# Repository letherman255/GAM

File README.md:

GAM
===

Projet terminale sti2d

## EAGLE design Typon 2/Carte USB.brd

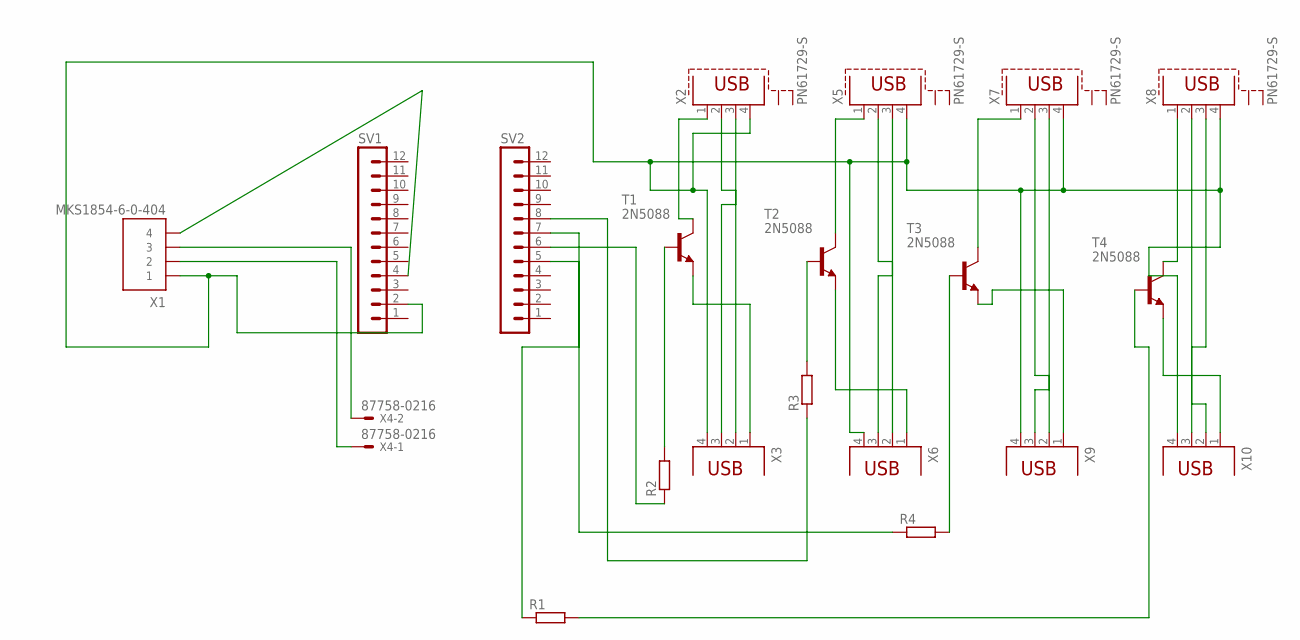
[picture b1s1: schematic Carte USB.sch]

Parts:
R1, R2, R3, R4: R-EU_0207/10; 0207/10
SV1, SV2: MA12-1
T1, T2, T3, T4: 2N5088; TO92
X1: MKS1854-6-0-404
X2, X5, X7, X8: PN61729-S
X3, X6, X9, X10: PN87520
X4: 87758-0216

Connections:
unnamed: X1.3, X4.2
unnamed: X1.2, X4.1
unnamed: T1.1 (C), X2.1
unnamed: X2.2, X3.2
unnamed: SV1.4, X1.4
unnamed: T2.1 (C), X5.1
unnamed: X2.3, X3.3
unnamed: X5.3, X6.3
unnamed: T2.3 (E), X6.1
unnamed: X5.2, X6.2
unnamed: T3.1 (C), X7.1
unnamed: X7.2, X9.2
unnamed: X7.3, X9.3
unnamed: T4.1 (C), X8.1
unnamed: X8.2, X10.2
unnamed: X8.3, X10.3
unnamed: SV1.2, X1.1, X2.4, X3.4, X5.4, X6.4, X7.4, X8.4, X9.4, X10.4
unnamed: T3.3 (E), X9.1
unnamed: T4.3 (E), X10.1
unnamed: T1.3 (E), X3.1
unnamed: R3.2, T2.2 (B)
unnamed: R4.2, T3.2 (B)
unnamed: R2.2, T1.2 (B)
unnamed: R1.2, T4.2 (B)
unnamed: R1.1, SV2.5
unnamed: R2.1, SV2.6
unnamed: R4.1, SV2.7
unnamed: R3.1, SV2.8

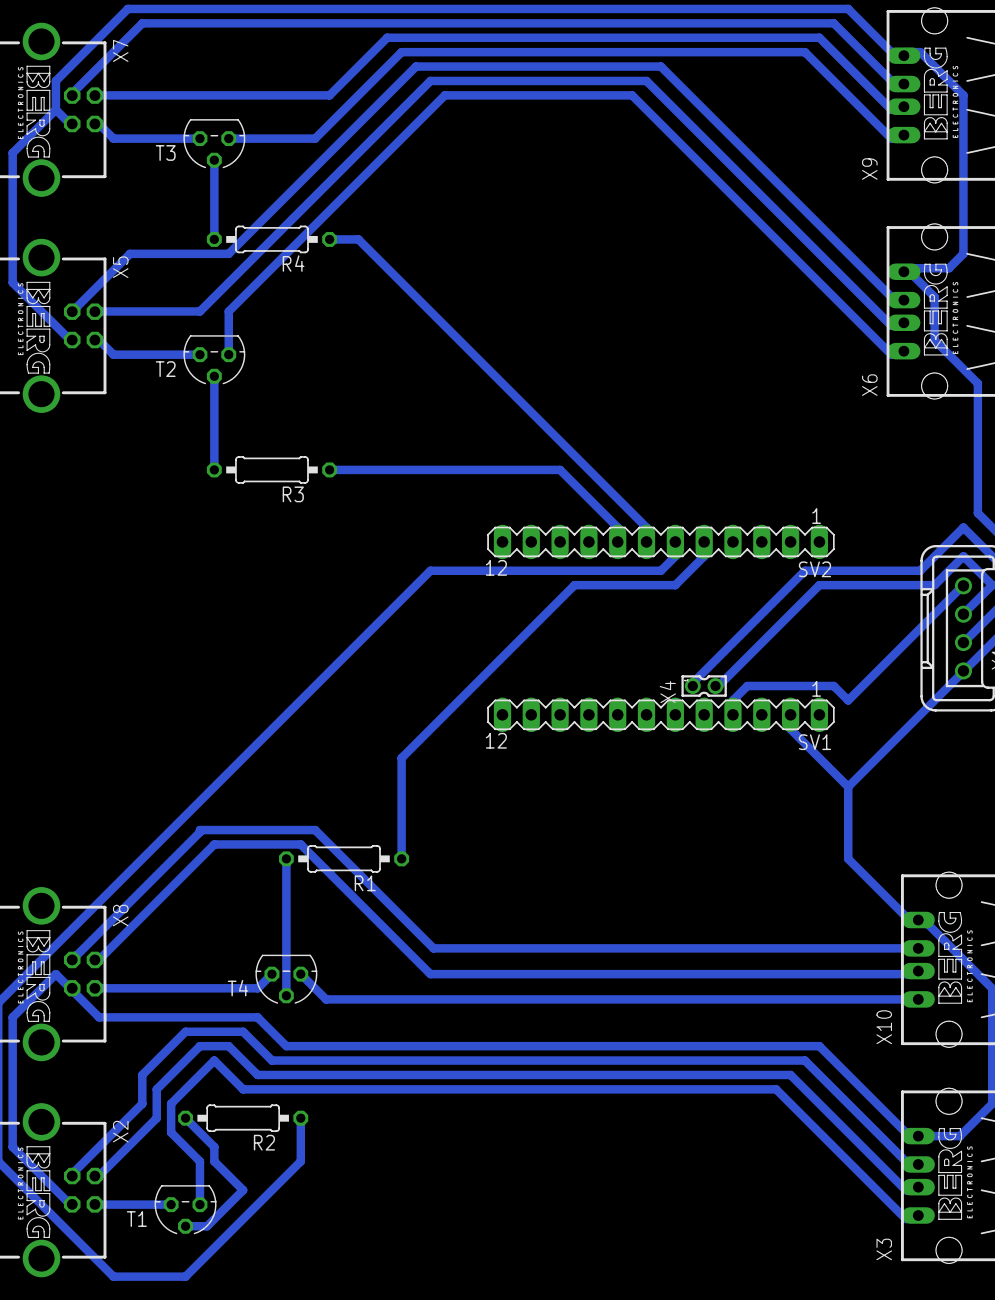
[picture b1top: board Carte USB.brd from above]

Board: 2 copper layers, 20 parts (0 on the bottom side), 28 nets.

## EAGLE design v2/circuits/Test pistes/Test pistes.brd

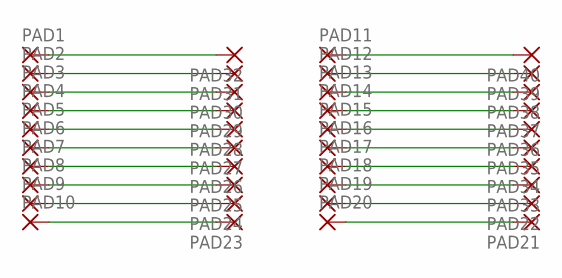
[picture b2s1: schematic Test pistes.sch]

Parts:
PAD1, PAD2, PAD3, PAD4, PAD5, PAD6, PAD7, PAD8, PAD9, PAD10, PAD11, PAD12, PAD13, PAD14, PAD15, PAD16, PAD17, PAD18, PAD19, PAD20, PAD21, PAD22, PAD23, PAD24, PAD25, PAD26, PAD27, PAD28, PAD29, PAD30, PAD31, PAD32, PAD33, PAD34, PAD35, PAD36, PAD37, PAD38, PAD39, PAD40: 2,54/1,1

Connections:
unnamed: PAD1.1, PAD32.1
unnamed: PAD2.1, PAD31.1
unnamed: PAD3.1, PAD30.1
unnamed: PAD4.1, PAD29.1
unnamed: PAD5.1, PAD28.1
unnamed: PAD6.1, PAD27.1
unnamed: PAD7.1, PAD26.1
unnamed: PAD8.1, PAD25.1
unnamed: PAD9.1, PAD24.1
unnamed: PAD10.1, PAD23.1
unnamed: PAD11.1, PAD40.1
unnamed: PAD12.1, PAD39.1
unnamed: PAD13.1, PAD38.1
unnamed: PAD14.1, PAD37.1
unnamed: PAD15.1, PAD36.1
unnamed: PAD16.1, PAD35.1
unnamed: PAD17.1, PAD34.1
unnamed: PAD18.1, PAD33.1
unnamed: PAD19.1, PAD22.1
unnamed: PAD20.1, PAD21.1

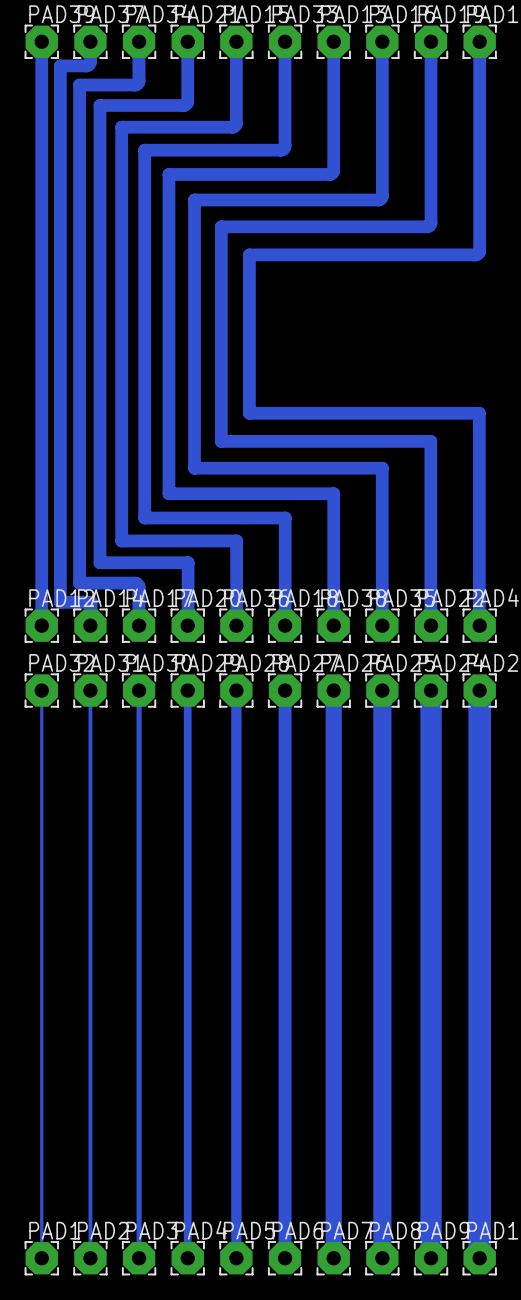
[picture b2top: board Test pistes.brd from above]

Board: 2 copper layers, 40 parts (0 on the bottom side), 20 nets.

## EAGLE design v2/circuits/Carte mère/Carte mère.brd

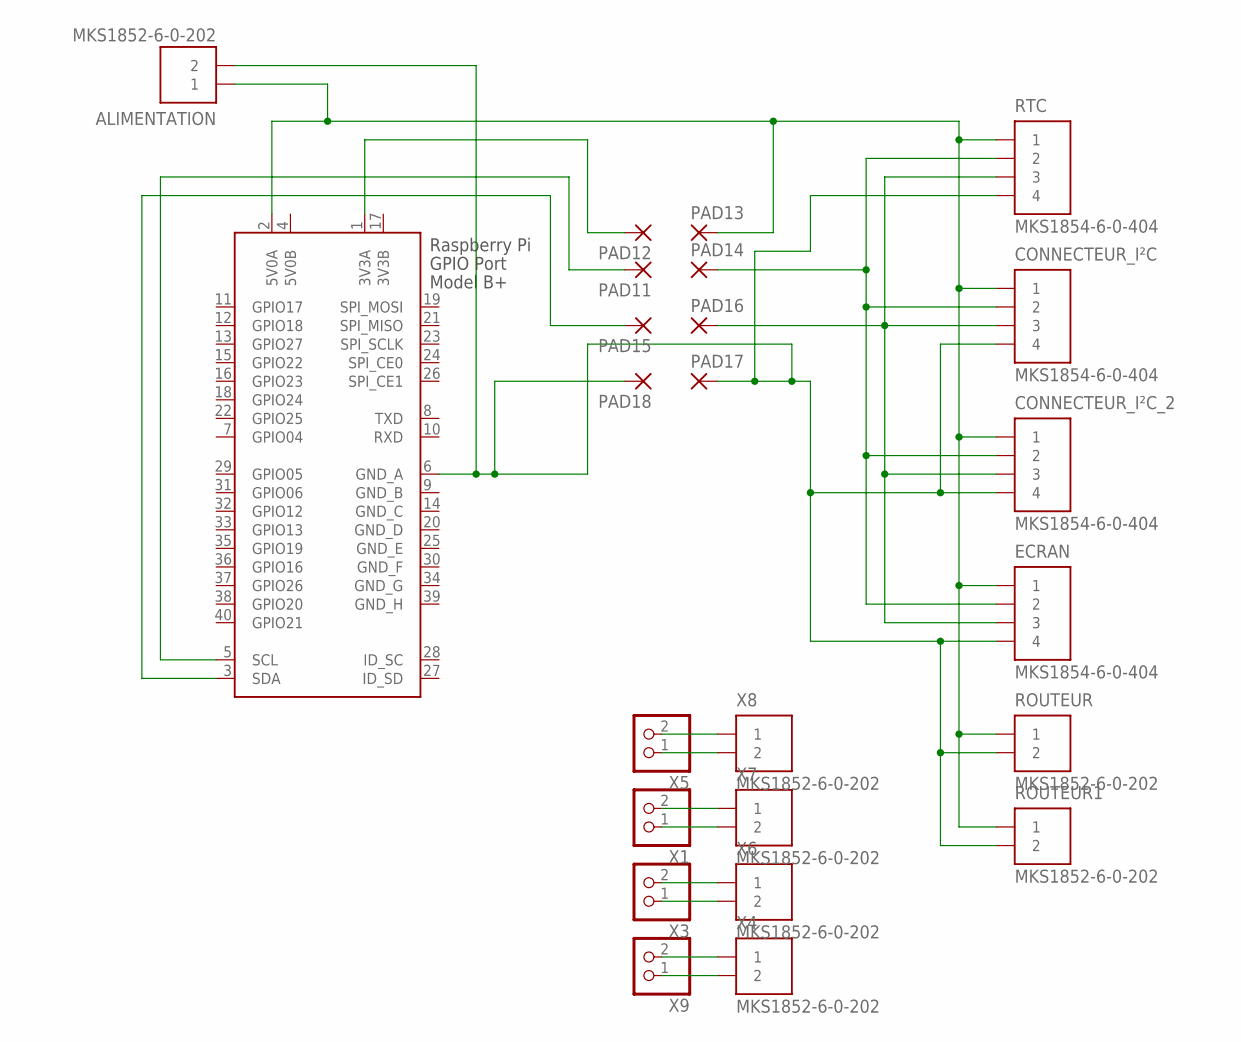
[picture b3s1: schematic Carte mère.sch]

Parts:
ALIMENTATION: MKS1852-6-0-202
CONNECTEUR_I²C: MKS1854-6-0-404
CONNECTEUR_I²C_2: MKS1854-6-0-404
ECRAN: MKS1854-6-0-404
PAD11, PAD12, PAD13, PAD14, PAD15, PAD16, PAD17, PAD18: 1,6/0,9
ROUTEUR, ROUTEUR1: MKS1852-6-0-202
RTC: MKS1854-6-0-404
X1, X3, X5, X9: PINHD-1X2; 1X02
X2: RASPI_GPIO_B+#_PIN; RASPI_GPIO_B+_PIN
X4, X6, X7, X8: MKS1852-6-0-202

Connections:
3V3B: X2.17 (3V3B)
5V0B: X2.4 (5V0B)
GND_B: X2.9 (GND_B)
GND_C: X2.14 (GND_C)
GND_D: X2.20 (GND_D)
GND_E: X2.25 (GND_E)
GND_F: X2.30 (GND_F)
GND_G: X2.34 (GND_G)
GND_H: X2.39 (GND_H)
unnamed: X5.2, X8.1
unnamed: ALIMENTATION.1, CONNECTEUR_I²C.1, CONNECTEUR_I²C_2.1, ECRAN.1, PAD13.1, ROUTEUR.1, ROUTEUR1.1, RTC.1, X2.2 (5V0A)
unnamed: X5.1, X8.2
unnamed: ALIMENTATION.2, CONNECTEUR_I²C.4, CONNECTEUR_I²C_2.4, ECRAN.4, PAD17.1, PAD18.1, ROUTEUR.2, ROUTEUR1.2, RTC.4, X2.6 (GND_A)
unnamed: X1.2, X7.1
unnamed: X1.1, X7.2
unnamed: X3.2, X6.1
unnamed: X3.1, X6.2
unnamed: X4.1, X9.2
unnamed: X4.2, X9.1
unnamed: PAD15.1, X2.3 (SDA)
unnamed: PAD11.1, X2.5 (SCL)
unnamed: PAD12.1, X2.1 (3V3A)
unnamed: CONNECTEUR_I²C.2, CONNECTEUR_I²C_2.2, ECRAN.2, PAD14.1, RTC.2
unnamed: CONNECTEUR_I²C.3, CONNECTEUR_I²C_2.3, ECRAN.3, PAD16.1, RTC.3

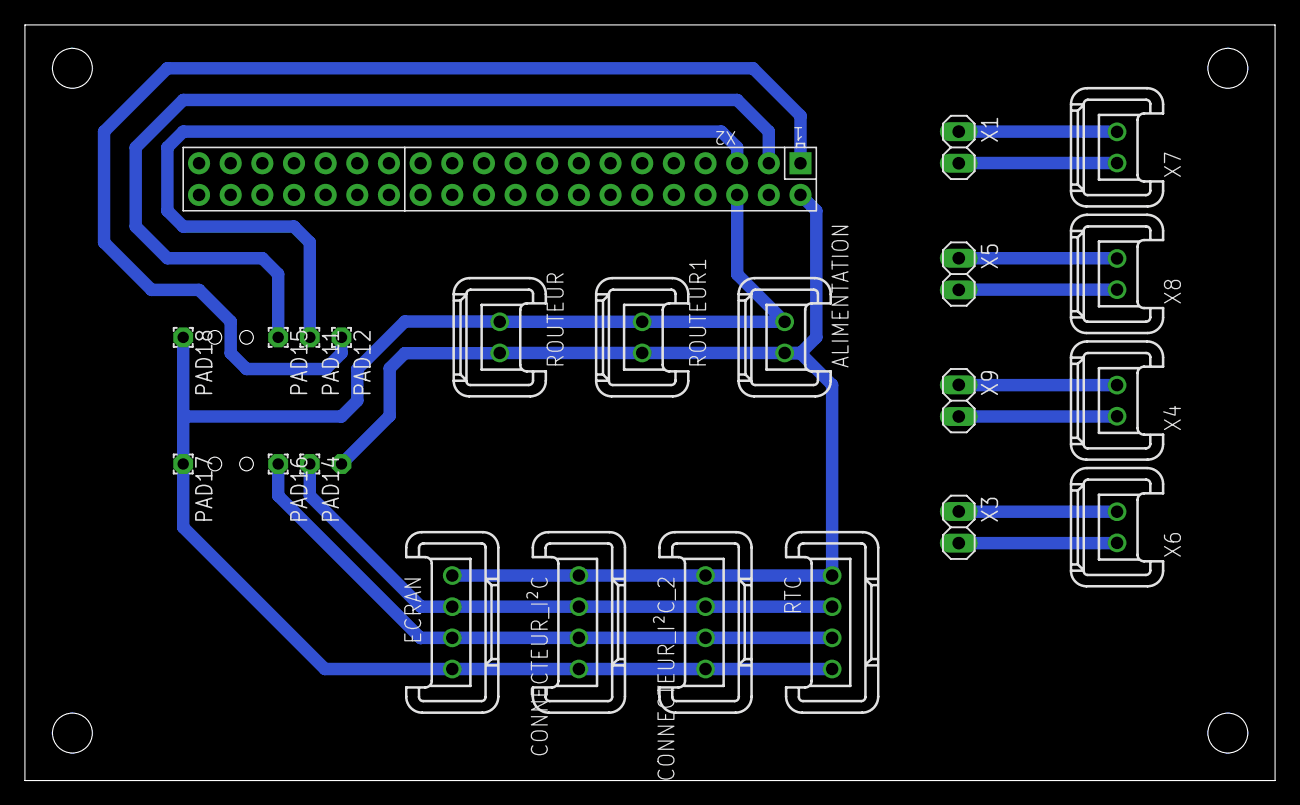
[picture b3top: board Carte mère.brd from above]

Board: 2 copper layers, 100.3 x 60.6 mm, 24 parts (1 on the bottom side), 15 nets.

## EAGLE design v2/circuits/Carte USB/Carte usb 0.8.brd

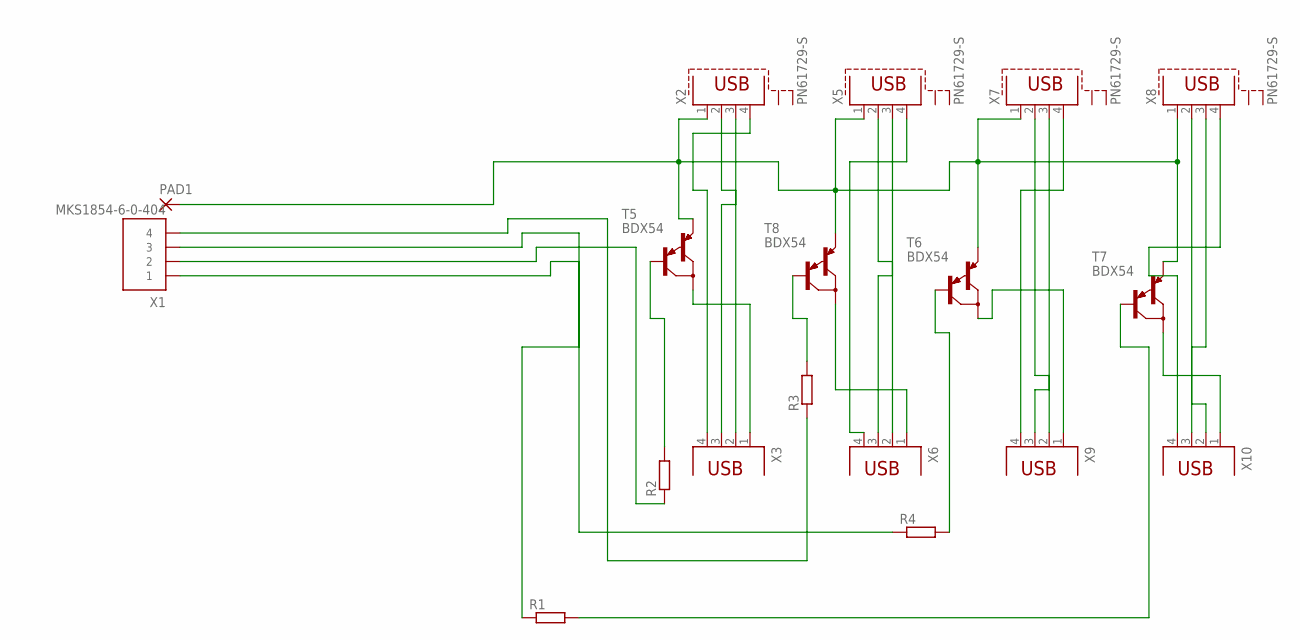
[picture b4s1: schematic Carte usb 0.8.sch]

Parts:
PAD1: 2,54/1,1
R1, R2, R3, R4: R-EU_0207/10; 0207/10
T5, T6, T7, T8: BDX54; TO220
X1: MKS1854-6-0-404
X2, X5, X7, X8: PN61729-S
X3, X6, X9, X10: PN87520

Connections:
unnamed: R2.2, T5.1 (B)
unnamed: R3.2, T8.1 (B)
unnamed: X2.2, X3.2
unnamed: R4.2, T6.1 (B)
unnamed: X2.3, X3.3
unnamed: X5.3, X6.3
unnamed: T8.2 (C), X6.1
unnamed: X5.2, X6.2
unnamed: X7.2, X9.2
unnamed: X2.4, X3.4
unnamed: X7.3, X9.3
unnamed: PAD1.1, T5.3 (E), T6.3 (E), T7.3 (E), T8.3 (E), X2.1, X5.1, X7.1, X8.1
unnamed: X8.2, X10.2
unnamed: X8.3, X10.3
unnamed: X8.4, X10.4
unnamed: X5.4, X6.4
unnamed: T6.2 (C), X9.1
unnamed: T7.2 (C), X10.1
unnamed: X7.4, X9.4
unnamed: T5.2 (C), X3.1
unnamed: R1.2, T7.1 (B)
unnamed: R1.1, X1.1
unnamed: R2.1, X1.2
unnamed: R4.1, X1.3
unnamed: R3.1, X1.4

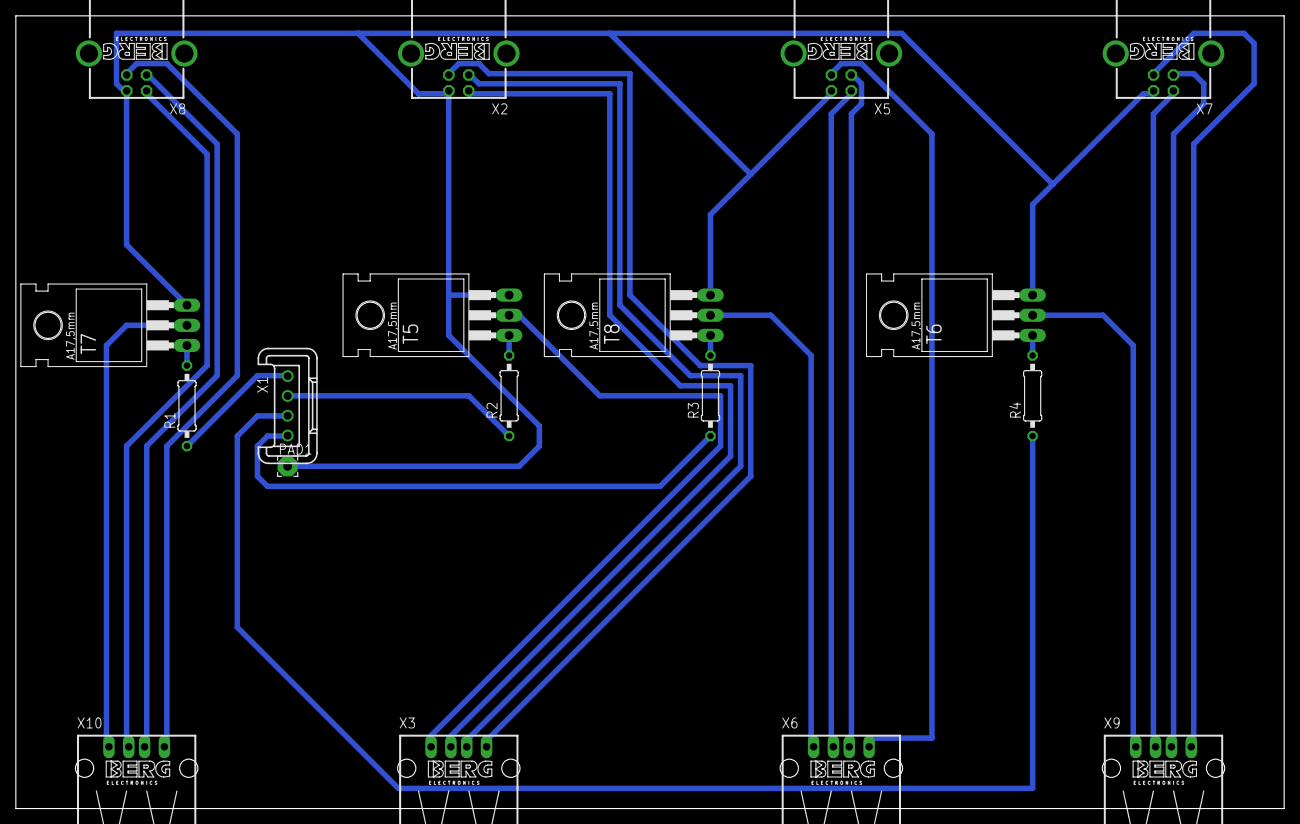
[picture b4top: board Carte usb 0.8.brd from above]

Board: 2 copper layers, 160.0 x 100.0 mm, 18 parts (0 on the bottom side), 25 nets.

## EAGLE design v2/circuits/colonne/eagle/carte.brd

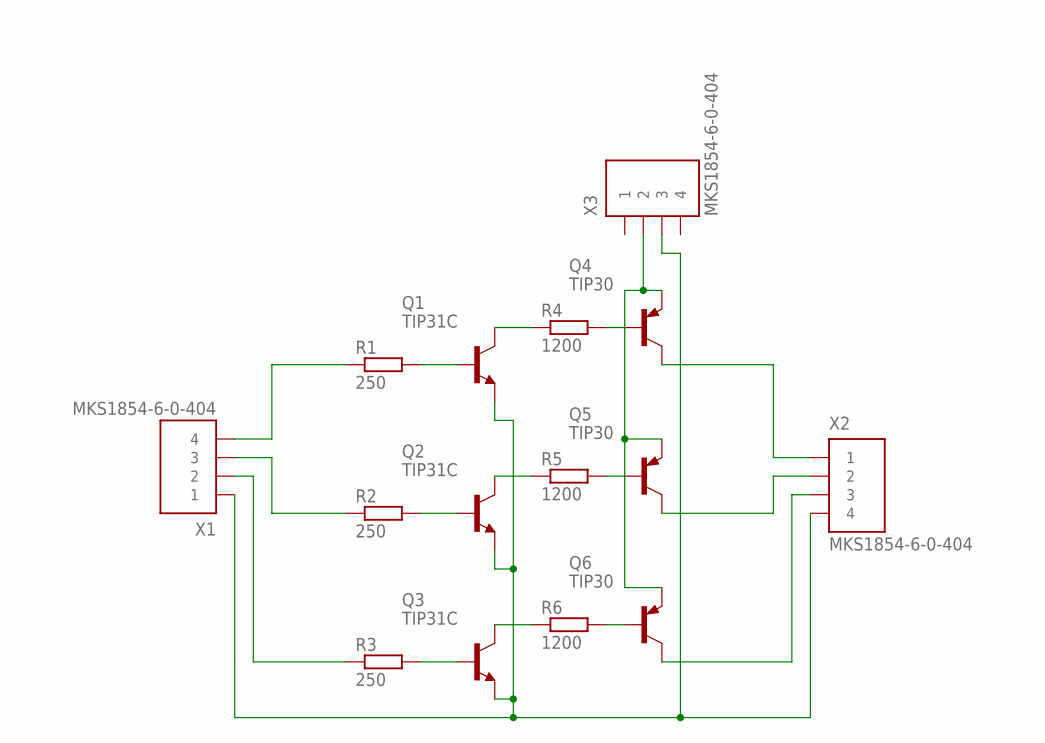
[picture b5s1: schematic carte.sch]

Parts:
Q1, Q2, Q3: TIP31C; TO220
Q4, Q5, Q6: TIP30; TO220
R1, R2, R3: 250; 0207/10
R4, R5, R6: 1200; 0207/10
X1, X2, X3: MKS1854-6-0-404

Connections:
unnamed: Q1.1 (B), R1.2
unnamed: Q2.1 (B), R2.2
unnamed: Q3.1 (B), R3.2
unnamed: Q1.2 (C), R4.1
unnamed: Q2.2 (C), R5.1
unnamed: Q3.2 (C), R6.1
unnamed: Q4.1 (B), R4.2
unnamed: Q5.1 (B), R5.2
unnamed: Q6.1 (B), R6.2
unnamed: Q1.3 (E), Q2.3 (E), Q3.3 (E), X1.1, X2.4, X3.3
unnamed: R1.1, X1.4
unnamed: R2.1, X1.3
unnamed: R3.1, X1.2
unnamed: Q4.3 (E), Q5.3 (E), Q6.3 (E), X3.2
unnamed: Q4.2 (C), X2.1
unnamed: Q5.2 (C), X2.2
unnamed: Q6.2 (C), X2.3

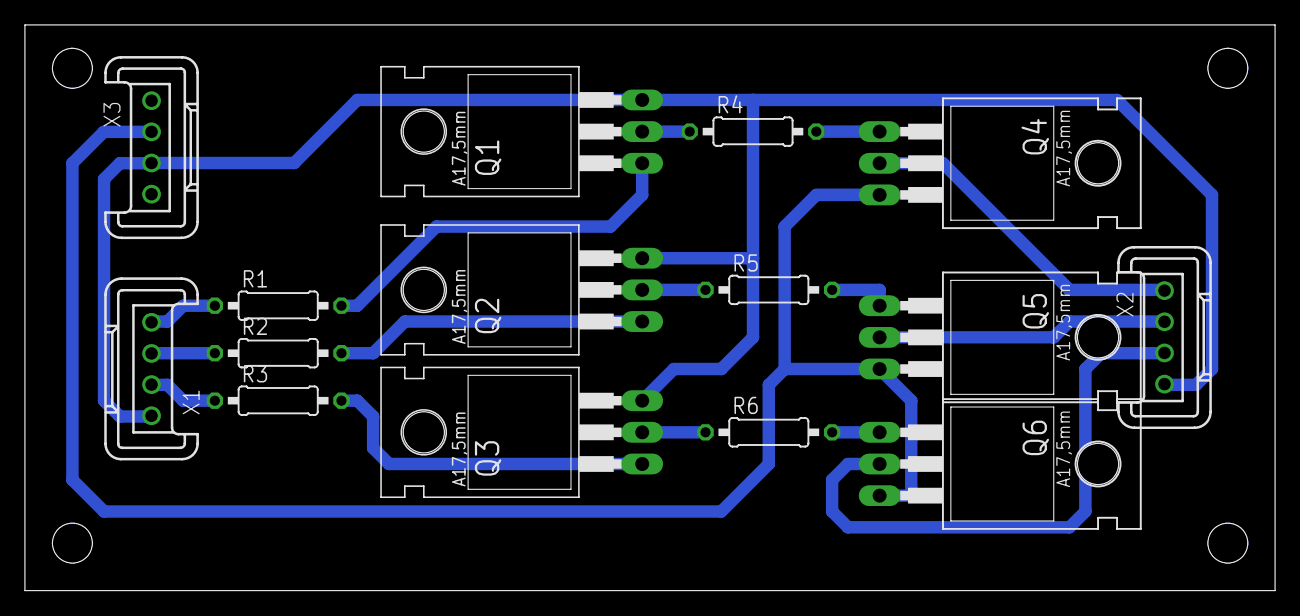
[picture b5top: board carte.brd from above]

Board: 2 copper layers, 100.3 x 45.4 mm, 15 parts (0 on the bottom side), 17 nets.

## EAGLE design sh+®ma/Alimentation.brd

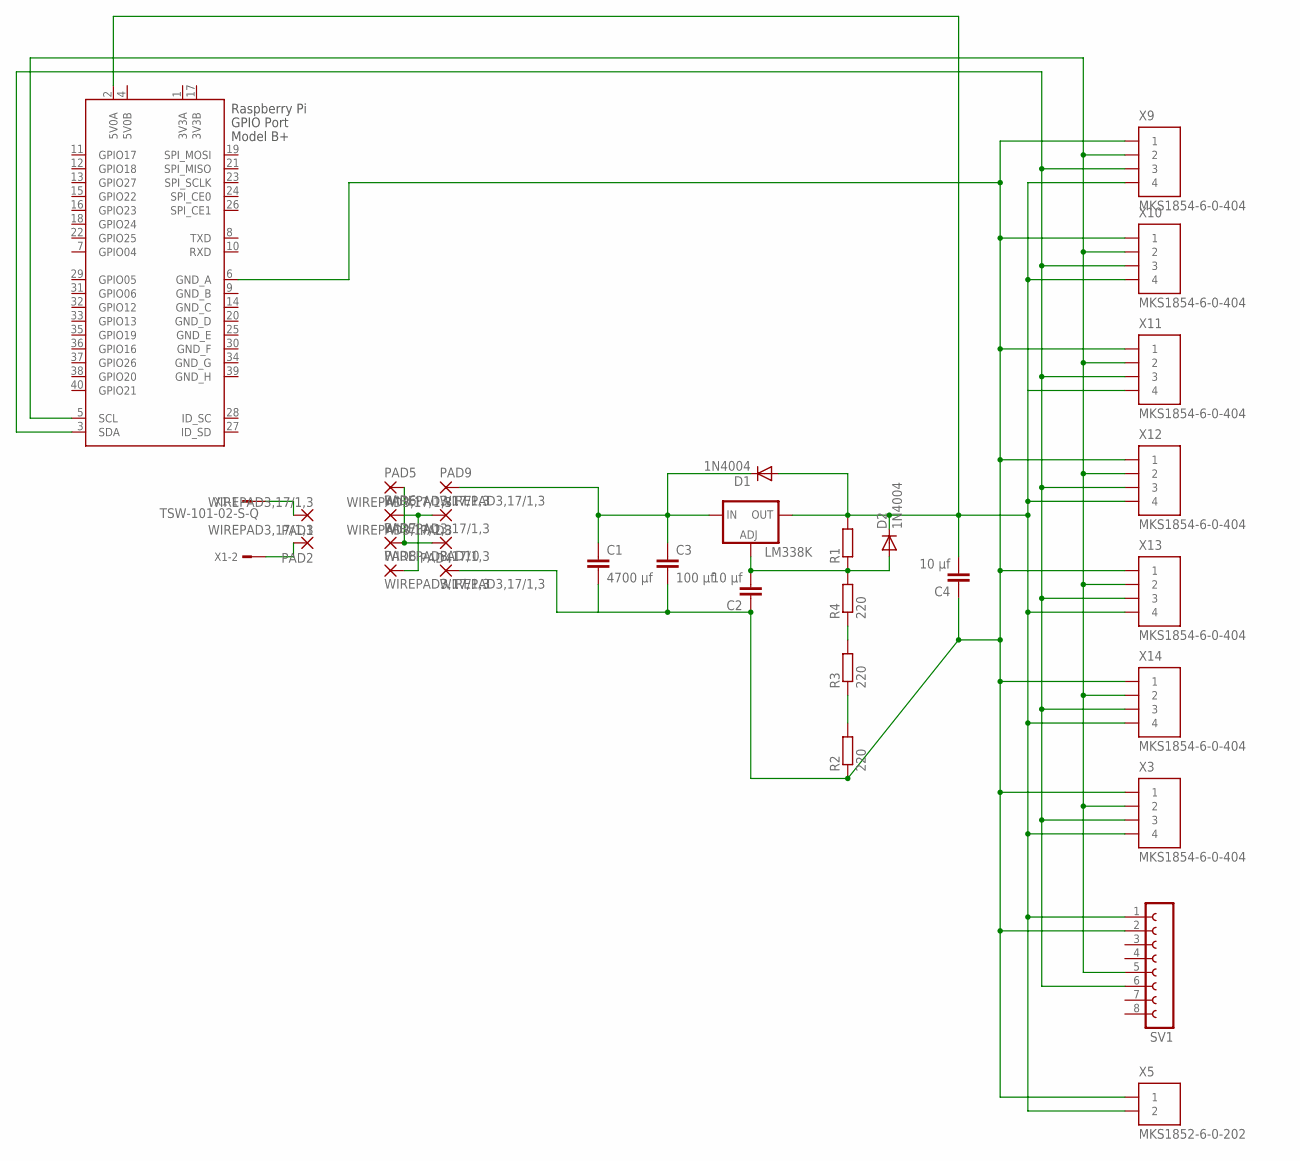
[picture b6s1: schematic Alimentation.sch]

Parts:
C1: 4700 µf; C075-032X103
C2, C4: 10 µf; C22.5B6
C3: 100 µf; C050-075X075
D1, D2: 1N4004; DO41-10
LM338K: LM317-TO3; TO3-K02
PAD1, PAD2, PAD3, PAD4, PAD5, PAD6, PAD7, PAD8, PAD9, PAD10: WIREPAD3,17/1,3; 3,17/1,3
R1: R-EU_0309/12; 0309/12
R2, R3, R4: 220; 0309/12
SV1: FE08-1; FE08
X1: TSW-101-02-S-Q
X2: RASPI_GPIO_B+#_PIN; RASPI_GPIO_B+_PIN
X3, X9, X10, X11, X12, X13, X14: MKS1854-6-0-404
X5: MKS1852-6-0-202

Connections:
3V3A: X2.1 (3V3A)
3V3B: X2.17 (3V3B)
5V0B: X2.4 (5V0B)
GND_B: X2.9 (GND_B)
GND_C: X2.14 (GND_C)
GND_D: X2.20 (GND_D)
GND_E: X2.25 (GND_E)
GND_F: X2.30 (GND_F)
GND_G: X2.34 (GND_G)
GND_H: X2.39 (GND_H)
unnamed: PAD1.1, X1.1
unnamed: PAD2.1, X1.2
unnamed: C1.2, C2.1, C3.2, C4.1, PAD10.1, R2.1, SV1.2, X2.6 (GND_A), X3.1, X5.1, X9.1, X10.1, X11.1, X12.1, X13.1, X14.1
unnamed: C1.1, C3.1, D1.C, LM338K.1 (IN), PAD9.1
unnamed: PAD3.1, PAD6.1, PAD8.1
unnamed: PAD4.1, PAD5.1, PAD7.1
unnamed: SV1.6, X2.3 (SDA), X3.3, X9.3, X10.3, X11.3, X12.3, X13.3, X14.3
unnamed: C2.2, D2.A, LM338K.2 (ADJ), R1.1, R4.2
unnamed: R2.2, R3.1
unnamed: C4.2, D1.A, D2.C, LM338K.3 (OUT), R1.2, SV1.1, X2.2 (5V0A), X3.4, X5.2, X9.4, X10.4, X11.4, X12.4, X13.4, X14.4
unnamed: R3.2, R4.1
unnamed: SV1.5, X2.5 (SCL), X3.2, X9.2, X10.2, X11.2, X12.2, X13.2, X14.2

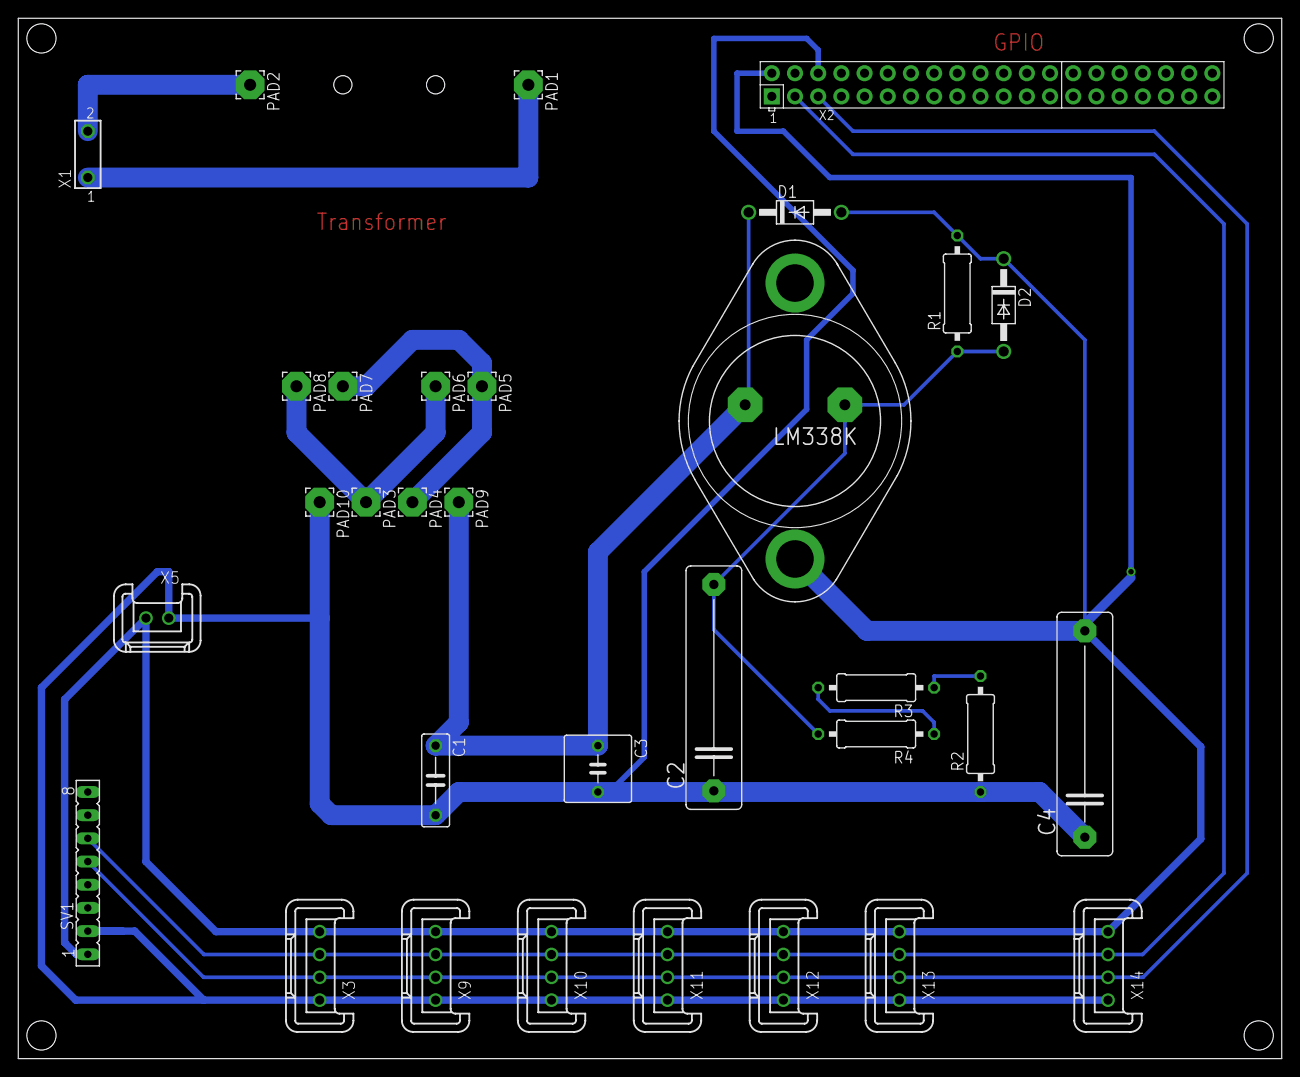
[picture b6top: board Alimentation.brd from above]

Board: 2 copper layers, 138.4 x 114.0 mm, 32 parts (0 on the bottom side), 12 nets.

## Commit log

2014-10-18 test de commit
2014-10-19 commit de ^merde de vic
2014-10-19 created modelio workspace
2014-10-19 updated project
2014-10-19 commuit
    commity
2014-10-19 added gitignore
2014-10-19 lock.info
2014-10-19 updated lock.info
2014-10-19 opened project
2014-10-19 mod git ignore
2014-10-19 mod gitignore
2014-10-19 added sys-ml lib
2014-10-19 Tâche
2014-10-19 test
2014-10-19 some work
2014-10-19 work
2014-10-19 updated ingore
2014-10-19 removed shit
2014-10-19 Suppress
2014-10-19 modelio 2.2.2
2014-10-19 remove
2014-10-19 git ignore
2014-10-19 ingore
2014-10-19 ignore
2014-10-19 modelio
    rien
2014-10-25 post
2014-10-25 gitignore
2014-10-25 premier requierment
2014-10-25 travail sur requirements
2014-10-25 exta
2014-11-05 topcased
    new topcased
2014-11-08 added usecase
2014-11-08 ignre
2014-11-08 added
2014-11-08 Requirement
2014-11-10 Requierment suite
2014-11-11 work on requirement
2014-11-11 Work and work
2014-11-11 added overview diagram
2014-11-11 Ressources
2014-11-11 Sysml
    Partie sécurité
2014-11-11 analyse fonctionnelle partie 1*
2014-11-11 analyse
2014-11-11 updated diagram
2014-11-11 Cahier des charges
    Tentative en étant "seul", vous plaigniez pas si j'ai fait de la merde
2014-11-14 Travail au lycée
    Avancement du Sysml et de l'analyse fonctionelle
2014-11-18 Travail au lycée
    modification du sysml
2014-11-18 dernière version analyse fonctionelle
2014-11-20 Analyse fonctionnelle et Diagrammes
2014-11-21 Analyse fonctionnelle (lycée)
2014-11-22 Travail au lycée et réorganisation des dossiers
    Création des dossiers personnels et d'une nouvelle workspace plus
    structurée.
2014-11-22 Revert "Travail au lycée et réorganisation des dossiers"
    This reverts commit 68e5f22d95b2afacb59acedf15d5a33ef01fe635.
2014-11-22 Réorganisation des dossiers
    J'ai revert mon commit car j'avais de prendre en compte la dernière
    version de l'analyse fonctionelle de Nico
2014-11-22 Ajout des nouveau dossiers
    Les fichiers texte nommé "Apparition" sont juste là pour que les
    dossiers vides apparaissent
2014-11-28 Travail eu lycée
    Amélioration de l'analyse fonctionelle et traduction de du requierement
2014-11-28 Analyse fonctionnelle (fin)
    Reste que les recherches de solutions
2014-12-04 Travail au lycée
    Début du diagramme de block et colorisation du requierement (je laisse
    le soin à Nico de commit l'analyse fonctionelle)
2014-12-06 Planning et analyse
2014-12-07 SYSML
    Ajout de quelque requierement et colorisation
2014-12-19 added java system
2014-12-19 Created web application
2014-12-20 Sysml
2014-12-20 gpio libs
2014-12-21 worked on java ee
2014-12-22 first GPIO control via webapp !
    -installed tomcat on raspberry
    -installed java on raspberry
    -installed libs on raspberry
2014-12-26 worked on website !
    +added proper html
    +added css
    +renamed Test.jsp -> admin.jsp
2014-12-26 icon for the website
2014-12-27 worked on admin panel (web)
    +added seperate table commands
2014-12-27 logic view diagram
2014-12-28 learning java ee
2015-01-01 moved tests to a seperate projects
2015-01-04 diagram
    worked on logic java ee view
2015-01-04 fin du diagramme
2015-01-10 system beans
    added System1 2 3 4 beans
2015-01-11 a bit of work
2015-01-12 Site VDI
    Les images ne se charge pas mais c'est normal, c'est juste pas la même
    manière de mettre les chemins des images dans l'html pour apache
2015-01-13 Site VDI version finale
2015-01-13 recommit
2015-01-13 sync
2015-01-13 données
2015-01-13 travaux
2015-01-13 + image
2015-01-13 change
2015-01-13 more images
2015-01-13 web-inf
2015-01-13 acceuil
2015-01-13 resync
2015-01-13 text allign
2015-01-13 dernier commit
2015-01-13 site
2015-01-14 HTML
2015-01-23 Je suis un commit de la salle de SIN §
2015-01-23 little change
2015-01-23 Alimentaion 5V 4A
2015-01-28 rejout projet d'entrainement
2015-02-01 diagramme edraw
2015-02-01 more schéematics
2015-02-17 workon multitak
2015-02-18 travail sur les threads
2015-02-20 putain de bug enfin résolut ! thread de merdddde
2015-02-20 putain de thread de merde
2015-02-20 bug de github ?
2015-02-20 removed for github
2015-02-20 Forms
2015-02-21 work on db
2015-02-22 started over dao
2015-02-22 the registering system works !!!!!!
2015-02-22 translation + fixed unused imports + fsupresswarnings serials
2015-02-22 fixed find method + added test on username when registering
2015-02-23 Annotations + filter + connection
2015-02-23 universal method + added test on mdlid when registering
2015-02-24 user manager page + fixed find()
2015-02-25 Fixed Franglish and added SystemProperty config loader
2015-02-26 added permissions
2015-02-27 Dépoussiérage du SYSML
2015-02-27 fix
    -fixed npe on admin filter( npe after session expired)
    -added banners
2015-02-27 worked on admin interface
2015-03-01 admin interface now gets the data from the System thread
2015-03-01 System Config from web interface
    -Fixed properties file (always loaded default value)
    -Config file auto generates when not detected
    -set the configs from the web interface
2015-03-02 user interface
    +connected userinterface info to system thread
    + single command form style
2015-03-03 commit before test
2015-03-03 set SystemInfo by users + veryfy when users try to play
2015-03-05 added credit in database
    -system usermanager displays credit
    -userinterface displays the credit and creditmeter
    -verifys that a user has enough credit to play
2015-03-06 Bug Fix and JSTL
    -replaced System info by System Status
    the methods to search , set and kill the user are now inside System
    Status
    -Made a human convertion of the system name in the user interface
2015-03-08 UML modeling + simplified modeling +fixed bug
    errors not clearing after being displayed and therefore preventing
    anyone from playing
2015-03-09 Merge branch 'master' of https://github.com/letherman255/GAM
    Conflicts:
    pro/WebContent/WEB-INF/web.xml
    pro/src/fr/mcnanotech/bdd/TestJDBC.java
    pro/src/fr/mcnanotech/servlets/GestionTestJDBC.java
2015-03-11 added credit daily setter -> now giving credit when registering a user Signed-off-by: letherman255 <matboularot@yahoo.fr>
2015-03-12 added admin test on user deletion began manager Signed-off-by: letherman255 <matboularot@yahoo.fr>
2015-03-21 worked on timer
2015-03-22 Programme pour Arduino + Typon pour Alim (non fini)
2015-03-23 Carte USB
2015-03-23 Carte mère (résolution problème transfo)
2015-03-25 Plan du soutien de l'écran + carte mère + écran
2015-03-26 better java
    thx robin4002
2015-03-26 euh ?
2015-03-28 shutdown and restart commands +filter fix + admin interface
2015-03-28 added rasberry pi shutdown and restart commands
    + automated tomcat on boot
2015-03-29 fixed tomcat bug
2015-03-29 fixed timer problem
2015-04-04 typon + plaque fond
2015-04-04 Arduino
2015-04-04 tests on i2c
2015-04-05 raspberry i2c works
    added config israspberry
    added i2c to arduino
2015-04-13 added lcd
2015-04-14 little add
2015-04-15 magic Robin BIECHY
2015-04-22 PowerPoint pour les OSI
2015-04-24 Typon
2015-04-28 added front pannel
2015-05-02 circuit colonne
    simulation + typon de la colonne
2015-05-03 added credit periods
2015-05-13 added boards
2015-05-17 banc de démo
2015-06-11 mise à jour typon
2015-06-18 commit de test
